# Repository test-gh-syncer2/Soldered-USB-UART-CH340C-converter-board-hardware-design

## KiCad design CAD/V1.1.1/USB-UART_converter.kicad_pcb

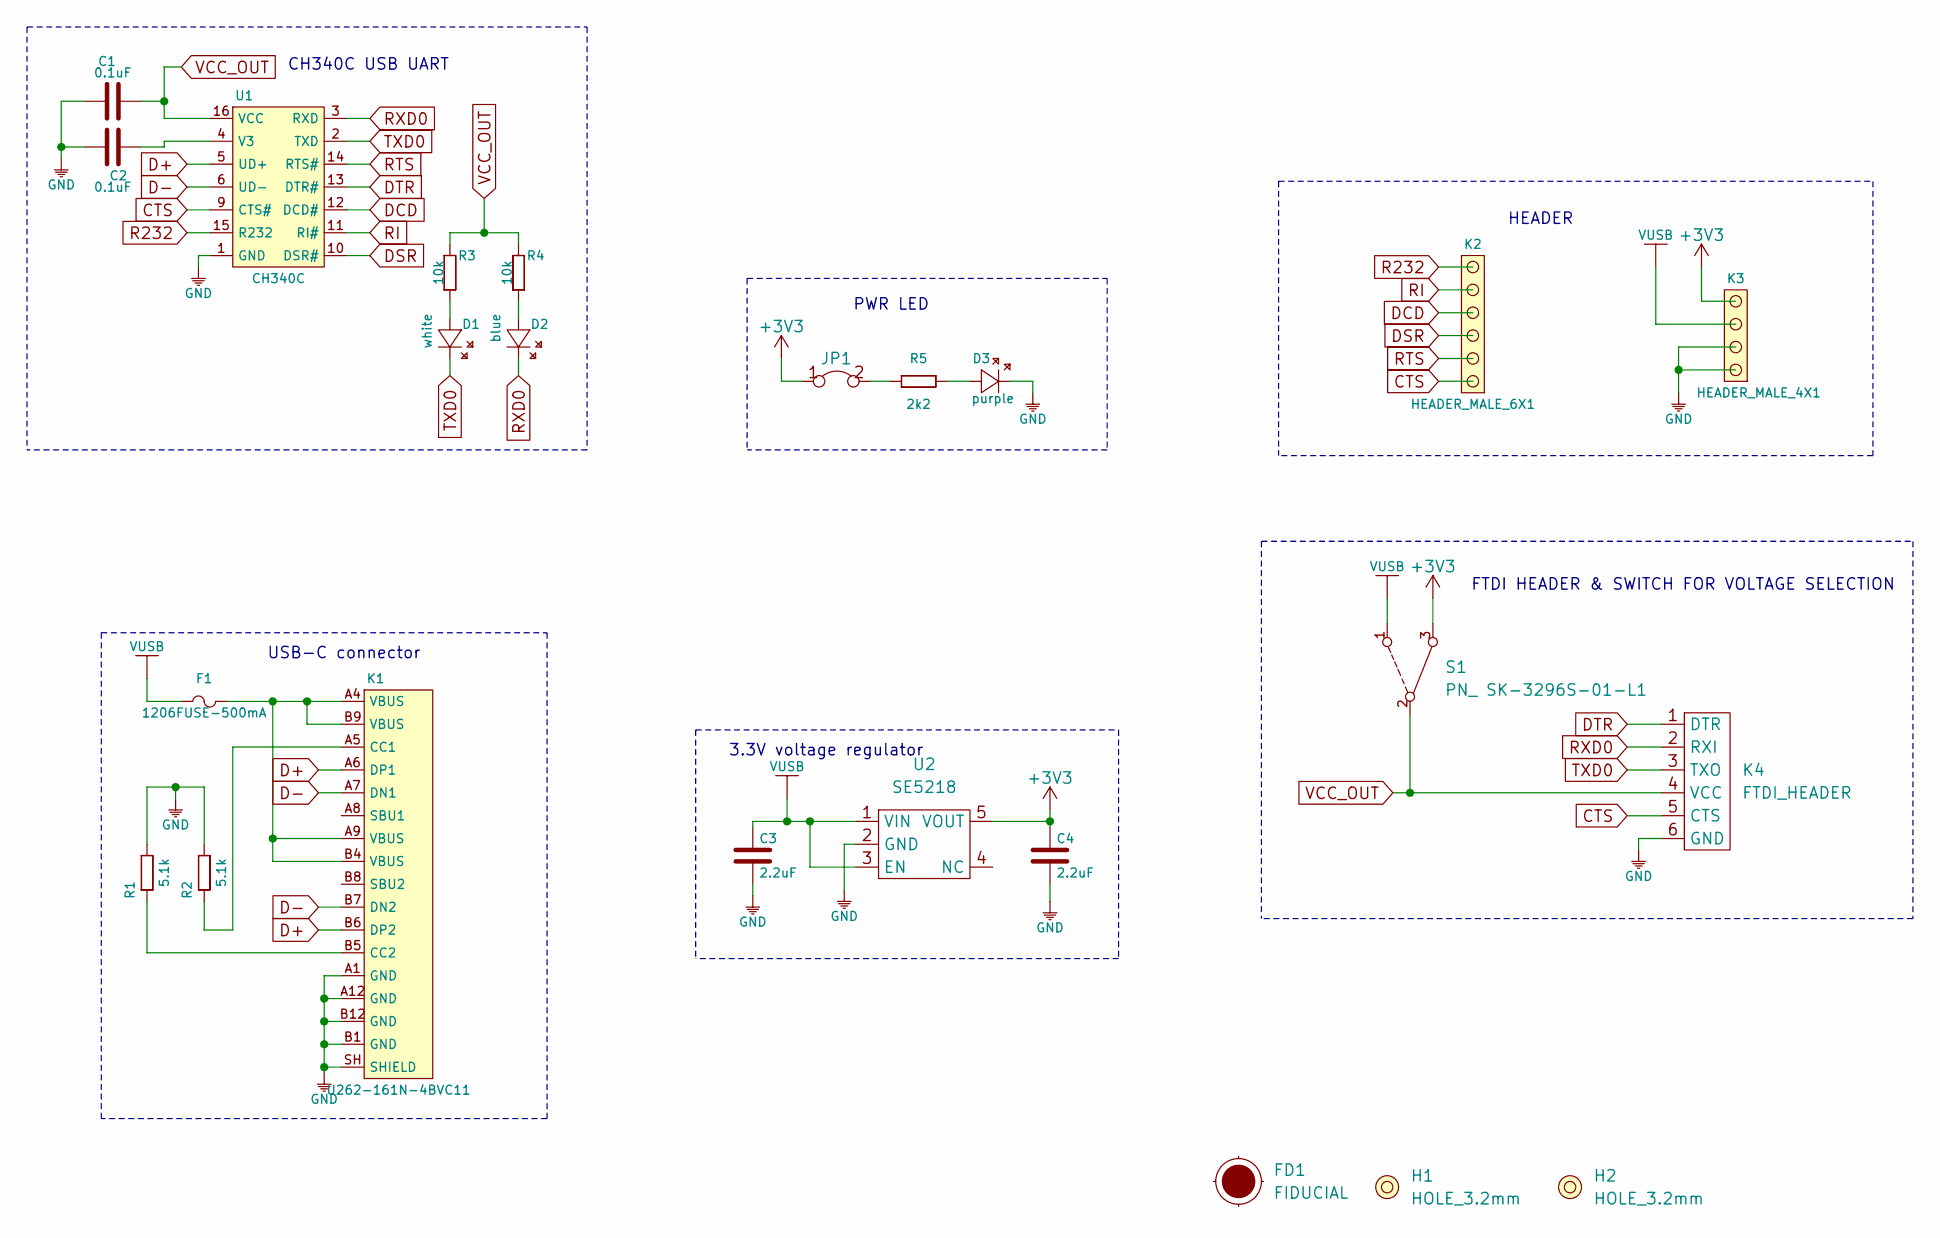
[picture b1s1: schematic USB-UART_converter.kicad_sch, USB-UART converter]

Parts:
C1, C2: 0.1uF; 0603C
C3, C4: 2.2uF; 0603C
D1: white; 0402LED
D2: blue; 0402LED
D3: purple; 0402LED
F1: 1206FUSE-500mA; 1206FUSE
FD1: FIDUCIAL; FIDUCIAL_23
H1, H2: HOLE_3.2mm
JP1: SMD-JUMPER-CONNECTED_TRACE_SLODERMASK
K1: U262-161N-4BVC11
K2: HEADER_MALE_6X1
K3: HEADER_MALE_4X1
K4: FTDI_HEADER; HEADER_MALE_6X1
R1, R2: 5.1k; 0603R
R3, R4: 10k; 0402R
R5: 2k2; 0402R
S1: PN_ SK-3296S-01-L1; SWITCH_ON_OFF_ON_3296
U1: CH340C; SOP-16
U2: SE5218; SOT-23-5

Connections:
+3V3: C4.2, JP1.1, K3.4, S1.3, U2.5 (VOUT)
CTS: K2.1, K4.5 (CTS), U1.9 (CTS#)
D+: K1.A6 (DP1), K1.B6 (DP2), U1.5 (UD+)
D-: K1.A7 (DN1), K1.B7 (DN2), U1.6 (UD-)
DCD: K2.4, U1.12 (DCD#)
DSR: K2.3, U1.10 (DSR#)
DTR: K4.1 (DTR), U1.13 (DTR#)
GND: C1.1, C2.2, C3.1, C4.1, D3.2 (K), K1.A1 (GND), K1.A12 (GND), K1.B1 (GND), K1.B12 (GND), K1.SH (SHIELD), K3.1, K3.2, K4.6 (GND), R1.2, R2.2, U1.1 (GND), U2.2 (GND)
unnamed: C2.1, U1.4 (V3)
unnamed: D1.1 (A), R3.1
unnamed: D2.1 (A), R4.1
unnamed: D3.1 (A), R5.2
unnamed: F1.2, K1.A4 (VBUS), K1.A9 (VBUS), K1.B4 (VBUS), K1.B9 (VBUS)
unnamed: JP1.2, R5.1
unnamed: K1.A5 (CC1), R2.1
unnamed: K1.B5 (CC2), R1.1
R232: K2.6, U1.15 (R232)
RI: K2.5, U1.11 (RI#)
RTS: K2.2, U1.14 (RTS#)
RXD0: D2.2 (K), K4.2 (RXI), U1.3 (RXD)
TXD0: D1.2 (K), K4.3 (TXO), U1.2 (TXD)
VCC_OUT: C1.2, K4.4 (VCC), R3.2, R4.2, S1.2, U1.16 (VCC)
VUSB: C3.2, F1.1, K3.3, S1.1, U2.1 (VIN), U2.3 (EN)

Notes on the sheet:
USB-C connector
CH340C USB UART
3.3V voltage regulator
PWR LED
HEADER
FTDI HEADER & SWITCH FOR VOLTAGE SELECTION

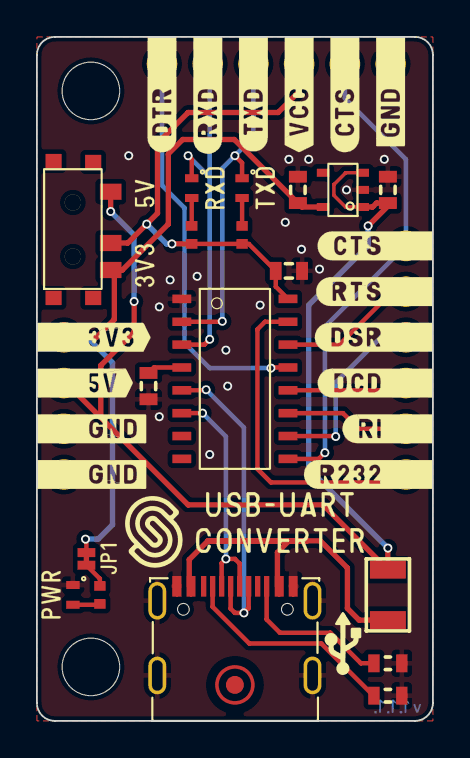
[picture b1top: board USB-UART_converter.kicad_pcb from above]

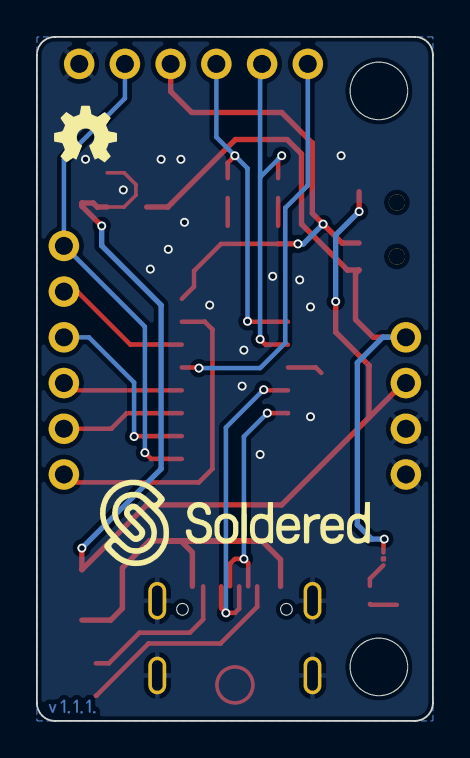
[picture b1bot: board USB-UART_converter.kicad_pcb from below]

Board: 2 copper layers, 22.0 x 38.0 mm, 24 parts (3 on the bottom side), 23 nets.

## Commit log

2021-09-23 Syncing to git
2021-09-23 Updating open source files.
